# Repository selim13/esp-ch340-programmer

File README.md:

# ESP8266/ESP32 programmer

A CH340T based programmer for ESP8266 and ESP32 with cross-transistor 
reset and boot mode circuit.

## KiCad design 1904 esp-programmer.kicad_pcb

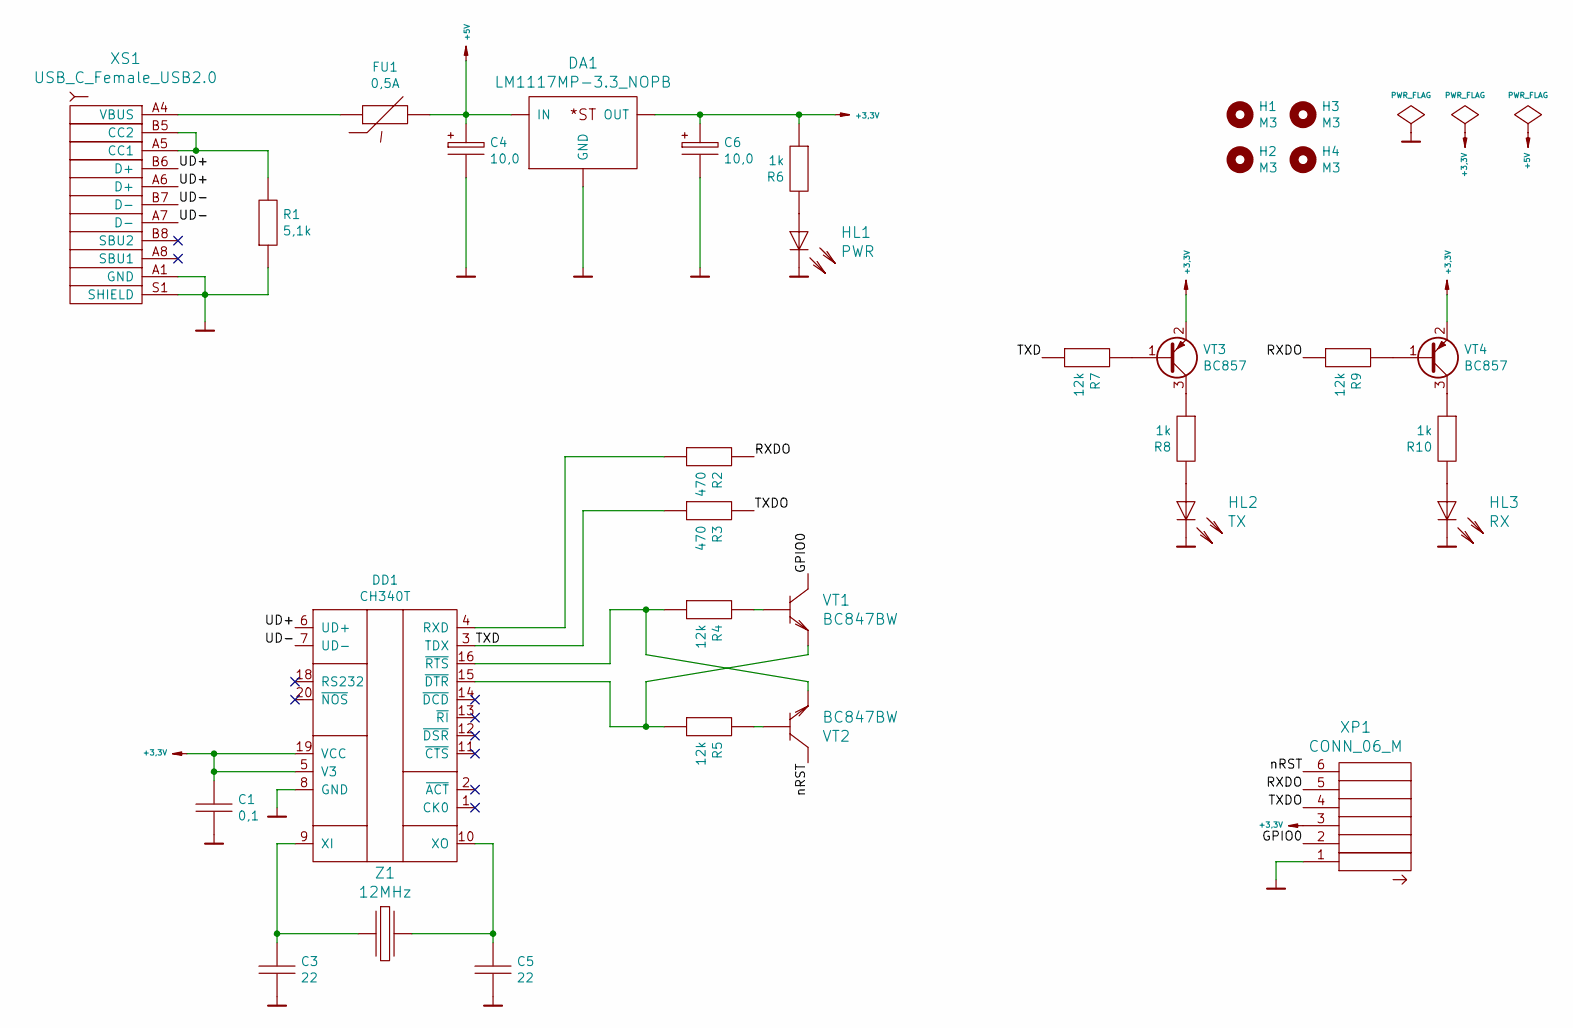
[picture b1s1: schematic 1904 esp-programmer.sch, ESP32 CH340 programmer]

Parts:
C1: 0,1; C_0805_2012Metric
C3, C5: 22; C_0805_2012Metric
C4, C6: 10,0; CP_EIA-3216-18_Kemet-A
DA1: LM1117MP-3.3_NOPB; SOT-223-3_TabPin2
DD1: CH340T; SSOP-20_5.3x7.2mm_P0.65mm
FU1: 0,5A; Fuse_1812_4532Metric
H1, H2, H3, H4: M3; MountingHole_3.2mm_M3
HL1: PWR; LED_0805_2012Metric
HL2: TX; LED_0805_2012Metric
HL3: RX; LED_0805_2012Metric
R1: 5,1k; R_0805_2012Metric
R2, R3: 470; R_0805_2012Metric
R4, R5, R7, R9: 12k; R_0805_2012Metric
R6, R8, R10: 1k; R_0805_2012Metric
VT1, VT2: BC847BW; SOT-323_SC-70
VT3, VT4: BC857; SOT-23
XP1: CONN_06_M; PinHeader_1x06_P2.54mm_Vertical
XS1: USB_C_Female_USB2.0; USB_C_Receptacle_USB2.0_16P
Z1: 12MHz; Crystal_HC49-4H_Vertical

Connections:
+3,3V: C1.1, C6.1, DA1.2 (OUT), DD1.5 (V3), DD1.19 (VCC), R6.2, VT3.2 (E), VT4.2 (E), XP1.3
+5V: C4.1, DA1.3 (IN), FU1.1
/GPIO0: VT1.3 (C), XP1.2
/RXDO: R2.1, R9.2, XP1.5
/TXD: DD1.3 (TDX), R3.2, R7.2
/TXDO: R3.1, XP1.4
/UD+: DD1.6 (UD+), XS1.A6 (D+), XS1.B6 (D+)
/UD-: DD1.7 (UD-), XS1.A7 (D-), XS1.B7 (D-)
/nRST: VT2.3 (C), XP1.6
GND: C1.2, C3.2, C4.2, C5.2, C6.2, DA1.1 (GND), DD1.8 (GND), HL1.1 (K), HL2.1 (K), HL3.1 (K), R1.2, XP1.1, XS1.A1 (GND), XS1.A12 (GND), XS1.B1 (GND), XS1.B12 (GND), XS1.S1 (SHIELD)
unnamed: C3.1, DD1.9 (XI), Z1.1
unnamed: C5.1, DD1.10 (XO), Z1.2
unnamed: DD1.4 (RXD), R2.2
unnamed: DD1.15 (~DTR), R5.2, VT1.2 (E)
unnamed: DD1.16 (~RTS), R4.2, VT2.2 (E)
unnamed: FU1.2, XS1.A4 (VBUS), XS1.A9 (VBUS), XS1.B4 (VBUS), XS1.B9 (VBUS)
unnamed: HL1.2 (A), R6.1
unnamed: HL2.2 (A), R8.1
unnamed: HL3.2 (A), R10.1
unnamed: R1.1, XS1.A5 (CC1), XS1.B5 (CC2)
unnamed: R4.1, VT1.1 (B)
unnamed: R5.1, VT2.1 (B)
unnamed: R7.1, VT3.1 (B)
unnamed: R8.2, VT3.3 (C)
unnamed: R9.1, VT4.1 (B)
unnamed: R10.2, VT4.3 (C)

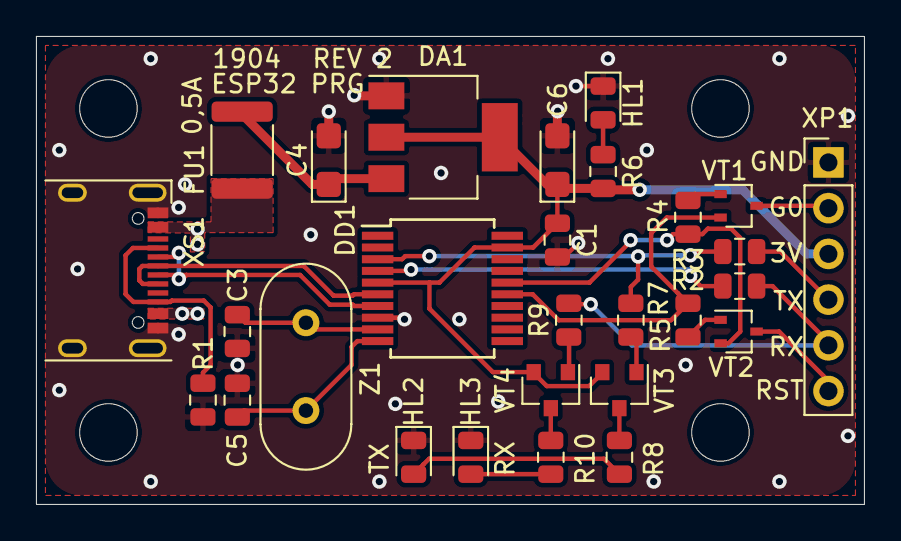
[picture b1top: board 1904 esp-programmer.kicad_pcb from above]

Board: 2 copper layers, 46.0 x 26.0 mm, 32 parts (0 on the bottom side), 26 nets.

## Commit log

2019-05-15 rev.2 initial commit
2019-05-15 add readme
